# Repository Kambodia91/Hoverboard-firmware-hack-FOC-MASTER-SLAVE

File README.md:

# Hoverboard firmware hack FOC MASTER/SLAVE (HOVER-1 RIVAL)

This repository implements Field Oriented Control (FOC) for hoverboards witch two boards Master and Slave. The boards communicate with each other via UART2, The motors are controlled via UART1 on the master board and Arduino. [Communication diagram](/docs/CommunicationDiagram) The left bldc motor was cut from the original program. 

The software is being tested.! More info: https://github.com/EFeru/hoverboard-firmware-hack-FOC/issues/364

---
YOUTUBE:
- [Test communication usart1 with esp32, blynkAPP](https://youtu.be/ViJhMbIGTzU).
- [Test safety communication](https://youtu.be/5jPmf3Z_Q6c).
- [Driving test 2 rear wheels](https://youtu.be/ALolYnv8E9s).
- [Driving test 01 4x4 new wheels](https://youtu.be/f5kqq9XtkOA?si=Ek2Kk6Emhx_Iep77).
- [Driving test 02 4x4 new wheels](https://youtu.be/5k37qx_ut7Y?si=PjrUhJfBA4WDzB2Y).
- [Drobiny test 03 with engine cutter](https://youtu.be/J5ug9tpqyGo?si=b4b2j3KFuMFDtWn7).
- [Cuttint height adjustment](https://youtu.be/1qUQQXA1uOE?si=6t5uq69G1FAZiTjl).
- [First cut grass](https://youtu.be/wi3ILRYedm8).
- [Alternator test V2](https://youtu.be/FKU_qiIISn4?si=lAowgcrbQPj_U_Ar).

---

Compared to the commutation method, this new FOC control method offers superior performance featuring:
 - reduced noise and vibrations 	
 - smooth torque output and improved motor efficiency. Thus, lower energy consumption
 - field weakening to increase maximum speed range

---
## Hardware
The originals are MM32 processors. We need to replace them with STM32. The program is used to support the [STM32F103CBT6](https://github.com/Kambodia91/Hoverboard-firmware-hack-FOC-MASTER-SLAVE/blob/main/docs/literature/STM32F103xB.pdf) processor. 
More information can be found in the [docs](/docs/).

Board pinouts: Slave / Master

---
## My Project
I am trying to create a 4-wheeled vehicle. Initial sketch idea:  (rigid without turning the wheels) using 2 howerboards for the wheels, communication will be made using uart and esp32. Currently, I was thinking about the actual position in space of the vehicle and came to the conclusion that the best solution would be to use the DW1000. In the future, there may be a lidar sensor. A lawn mower will be installed on the wheels to mow the lawn automatically. I invite you to the docs tab there are more [photos](/docs/pictures/) from the construction.

-- --

To do: 
- [x] Hack howerboard motherboards.  
- [x] Convert the LED Out socket to a USART1 socket for control.  
- [x] Change tire size.  
- [x] Extend the wheel current cables and the hall sensor signal.  
- [x] Insert the wheel controller into the housing.  
- [x] Make connections for programming and debugging without having to remove the boards.  
- [x] Vehicle frame structure.
- [x] Cutting height.
- [x] Installation of the combustion engine.
- [x] Making a hub to connect the alternator and the cutting knife.
- [x] Connecting the engine shaft with the alternator pulley with a multi-grooved belt.  
- [x] Converting a 12v alternator to 42v.  
- [x] Installing the alternator to the vehicle frame.
- [x] Selecting a remote control for manual control.
- [ ] Installation of a PIXHAWK controller for remote planning and autonomous mission
- [ ] Combine the GPS system with RTK correction to obtain high spatial orientation accuracy
- [ ] installation of sensors to avoid obstacles

---
## FOC Firmware
 
In this firmware 3 control types are available, it can be set in config.h file via CTRL_TYP_SEL parameter:
- Commutation (COM_CTRL)
- Sinusoidal (SIN_CTRL)
- Field Oriented Control (FOC_CTRL) with the following 3 control modes that can be set in config.h file with parameter CTRL_MOD_REQ:
  - **VOLTAGE MODE(VLT_MODE)**: in this mode the controller applies a constant Voltage to the motors. Recommended for robotics applications or applications where a fast motor response is required.
  - **SPEED MODE(SPD_MODE)**: in this mode a closed-loop controller realizes the input speed RPM target by rejecting any of the disturbance (resistive load) applied to the motor. Recommended for robotics applications or constant speed applications.
  - **TORQUE MODE(TRQ_MODE)**: in this mode the input torque target is realized. This mode enables motor "freewheeling" when the torque target is `0`. Recommended for most applications with a sitting human driver.

---
### FOC Webview

To explore the controller without a Matlab/Simulink installation click on the link below:

[https://eferu.github.io/bldc-motor-control-FOC/](https://eferu.github.io/bldc-motor-control-FOC/)

---
## Example Variants

- **VARIANT_ADC**: The motors are controlled by one potentiometer connected to the white cable (connector hall). EnableMotors will turn on automatically.

- **VARIANT_USART**: The motors are controlled via serial protocol (e.g. on USART1). The commands can be sent from an Arduino. Check out the [hoverserial](/Arduino/hoverserial.cpp) as an example sketch.

- **VARIANT_PPM**: RC remote control with PPM Sum signal. Reciver connect to pin RX USATR1. Ch1: MasterSpeed, Ch2: SlaveSpeed, Ch3: EnableMotors, Ch4: -, Ch5: Button1, Ch6: Button2. When Button_Support is disabled, EnnableMotors will be enabled automatically.
  
- **VARIANT_PWM:** RC remote control with PWM signal. PWM signal 1 (MasterSpeed) connect to TX USART1, PWM signal 2 (SlaveSpeed) connect to RX USART1. EnableMotors will turn on automatically.

Of course the firmware can be further customized for other needs or projects.

---
## Status

---
## Projects and Links

- **Original firmware:** [https://github.com/lucysrausch/hoverboard-firmware-hack](https://github.com/lucysrausch/hoverboard-firmware-hack)
- **[Candas](https://github.com/Candas1/) Hoverboard Web Serial Control:** [https://github.com/Candas1/Hoverboard-Web-Serial-Control](https://github.com/Candas1/Hoverboard-Web-Serial-Control)
- **[RoboDurden's](https://github.com/RoboDurden) online compiler:** [https://pionierland.de/hoverhack/](https://pionierland.de/hoverhack/) 
- **Hoverboard hack for AT32F403RCT6 mainboards:** [https://github.com/cloidnerux/hoverboard-firmware-hack](https://github.com/cloidnerux/hoverboard-firmware-hack)
- **Hoverboard hack for split mainboards:** [https://github.com/flo199213/Hoverboard-Firmware-Hack-Gen2](https://github.com/flo199213/Hoverboard-Firmware-Hack-Gen2)
- **Hoverboard hack from BiPropellant:** [https://github.com/bipropellant](https://github.com/bipropellant)
- **Hoverboard breakout boards:** [https://github.com/Jana-Marie/hoverboard-breakout](https://github.com/Jana-Marie/hoverboard-breakout)

<a/>

- **Bobbycar** [https://github.com/larsmm/hoverboard-firmware-hack-FOC-bbcar](https://github.com/larsmm/hoverboard-firmware-hack-FOC-bbcar)
- **Wheel chair:** [https://github.com/Lahorde/steer_speed_ctrl](https://github.com/Lahorde/steer_speed_ctrl)
- **TranspOtterNG:** [https://github.com/Jan--Henrik/transpOtterNG](https://github.com/Jan--Henrik/transpOtterNG)
- **Hoverboard driver for ROS:** [https://github.com/alex-makarov/hoverboard-driver](https://github.com/alex-makarov/hoverboard-driver)
- **Ongoing OneWheel project:** [https://forum.esk8.news/t/yet-another-hoverboard-to-onewheel-project/60979/14](https://forum.esk8.news/t/yet-another-hoverboard-to-onewheel-project/60979/14)
- **ST Community:** [Custom FOC motor control](https://community.st.com/s/question/0D50X0000B28qTDSQY/custom-foc-control-current-measurement-dma-timer-interrupt-needs-review)

<a/>

- **Telegram Community:** If you are an enthusiast join our [Hooover Telegram Group](https://t.me/joinchat/BHWO_RKu2LT5ZxEkvUB8uw)

---
## Contributions

Every contribution to this repository is highly appreciated! Feel free to create pull requests to improve this firmware as ultimately you are going to help everyone. 
---

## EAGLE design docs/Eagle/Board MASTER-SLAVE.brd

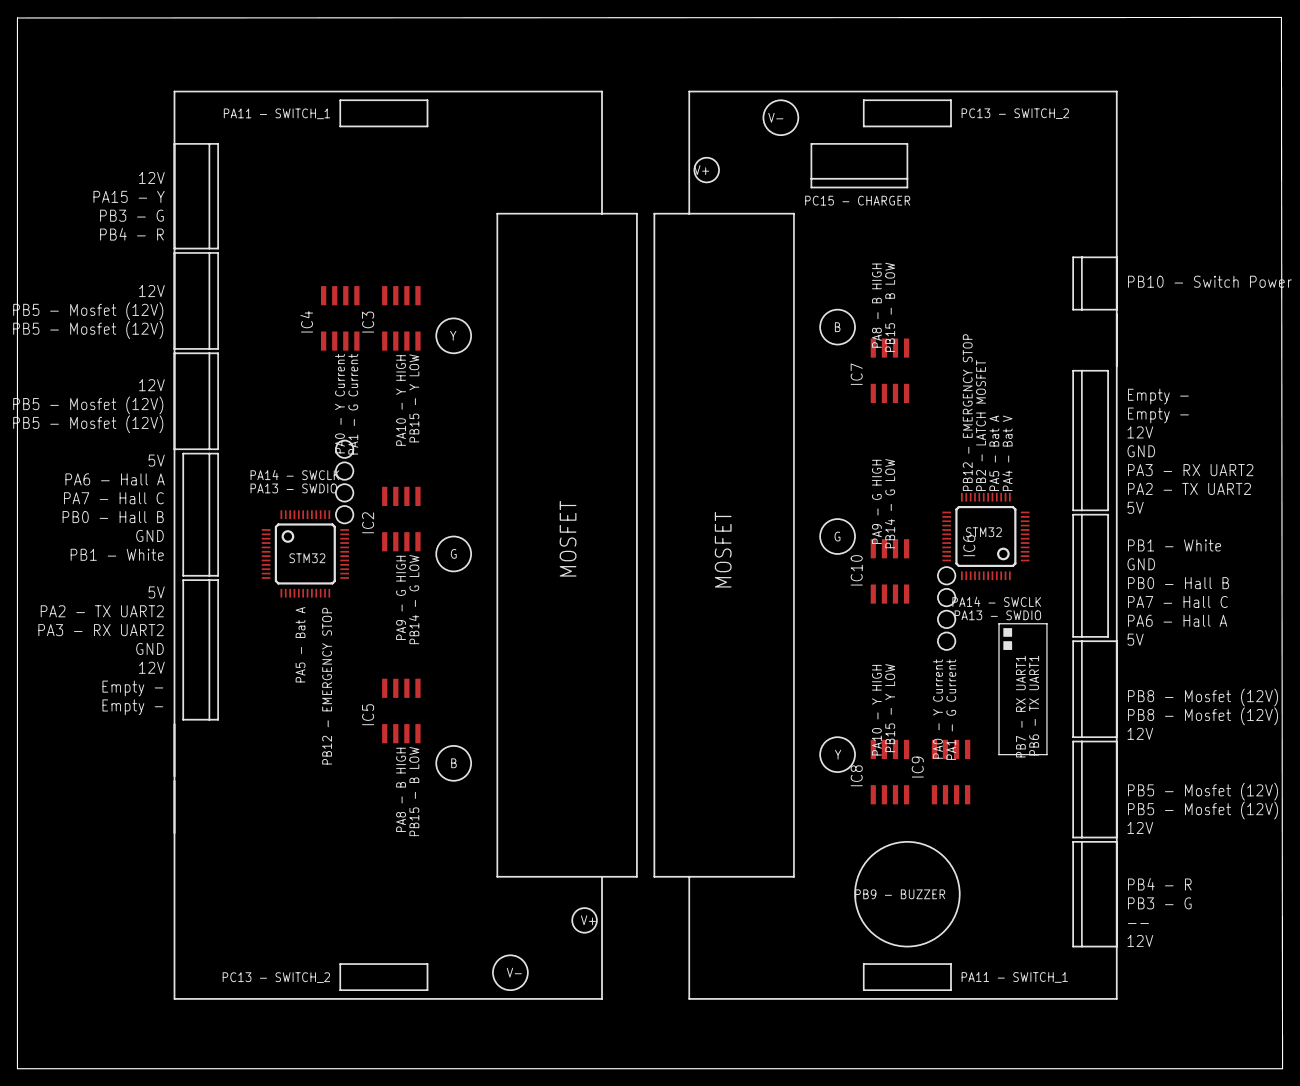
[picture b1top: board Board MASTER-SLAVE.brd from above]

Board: 2 copper layers, 145.0 x 120.5 mm, 10 parts (0 on the bottom side), 11 nets, no tracks yet.

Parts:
IC1, IC6: STM32F10XCXT6; TQFP48
IC2, IC3, IC4, IC5, IC7, IC8, IC9, IC10: USB6B1; SO08

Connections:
GND: IC2.4, IC2.5, IC3.4, IC3.5, IC4.4, IC4.5, IC5.4, IC5.5, IC7.4, IC7.5, IC8.4, IC8.5, IC9.4, IC9.5, IC10.4, IC10.5
VBAT: IC1.1, IC6.1
VCC: IC2.1, IC2.8, IC3.1, IC3.8, IC4.1, IC4.8, IC5.1, IC5.8, IC7.1, IC7.8, IC8.1, IC8.8, IC9.1, IC9.8, IC10.1, IC10.8
VDDA: IC1.9, IC6.9
VDD_1: IC1.24, IC6.24
VDD_2: IC1.36, IC6.36
VDD_3: IC1.48, IC6.48
VSSA: IC1.8, IC6.8
VSS_1: IC1.23, IC6.23
VSS_2: IC1.35, IC6.35
VSS_3: IC1.47, IC6.47

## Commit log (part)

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2023-02-06 add new files
2023-02-24 common
2023-03-08 add BKIN
2023-03-09 add new picture
2023-03-09 small changes
2023-03-14 add temp Mastae/Slave and enaboeMotors via uart1
2023-03-15 new picture
2023-04-04 change board
2023-04-25 add Communication
2023-04-25 more feedback
2023-04-25 add new communication
2023-04-28 cut left motor and add delay
2023-05-03 adds a new function "ControlMode"
2023-07-08 Update README.md
    Add link yt
2023-09-16 New photos, clean and test of new parameters
2023-10-07 Fixed bugs with new CPU programming
2023-10-08 work in progress
2023-10-11 add jest movies
2023-11-19 Add Disable Buzzer
2023-12-05 bug fixes
2023-12-11 add new box controler
2024-01-19 little change
2024-02-01 Add options Single Board Master
2024-02-15 fixed bug with first run
2024-02-28 ADC/PPM clean
2024-02-28 ADC Clean
2024-03-01 ADC & IBUS correct input
2024-03-02 TO DO
2024-03-05 updated to do
2024-03-06 ibus input correct
2024-03-28 new Photos
2024-04-04 add leds status
2024-04-04 err code M/S
2024-04-17 add movie alternatir
2025-02-20 added diode support WS2812b
2025-05-30 clean
2025-05-30 dma1 priority setting
2025-06-18 test
2025-06-21 ws2812 send if changed
2026-01-27 Update board variant definitions and adjust DMA interrupt priorities
2026-02-17 test comunication
2026-02-18 fixed communication between the boards
2026-02-20 Update board variant definitions and enhance motor control structure
2026-02-24 Refactor board variant handling and streamline motor control logic
2026-02-24 Update board variant definitions and improve LED handling logic
